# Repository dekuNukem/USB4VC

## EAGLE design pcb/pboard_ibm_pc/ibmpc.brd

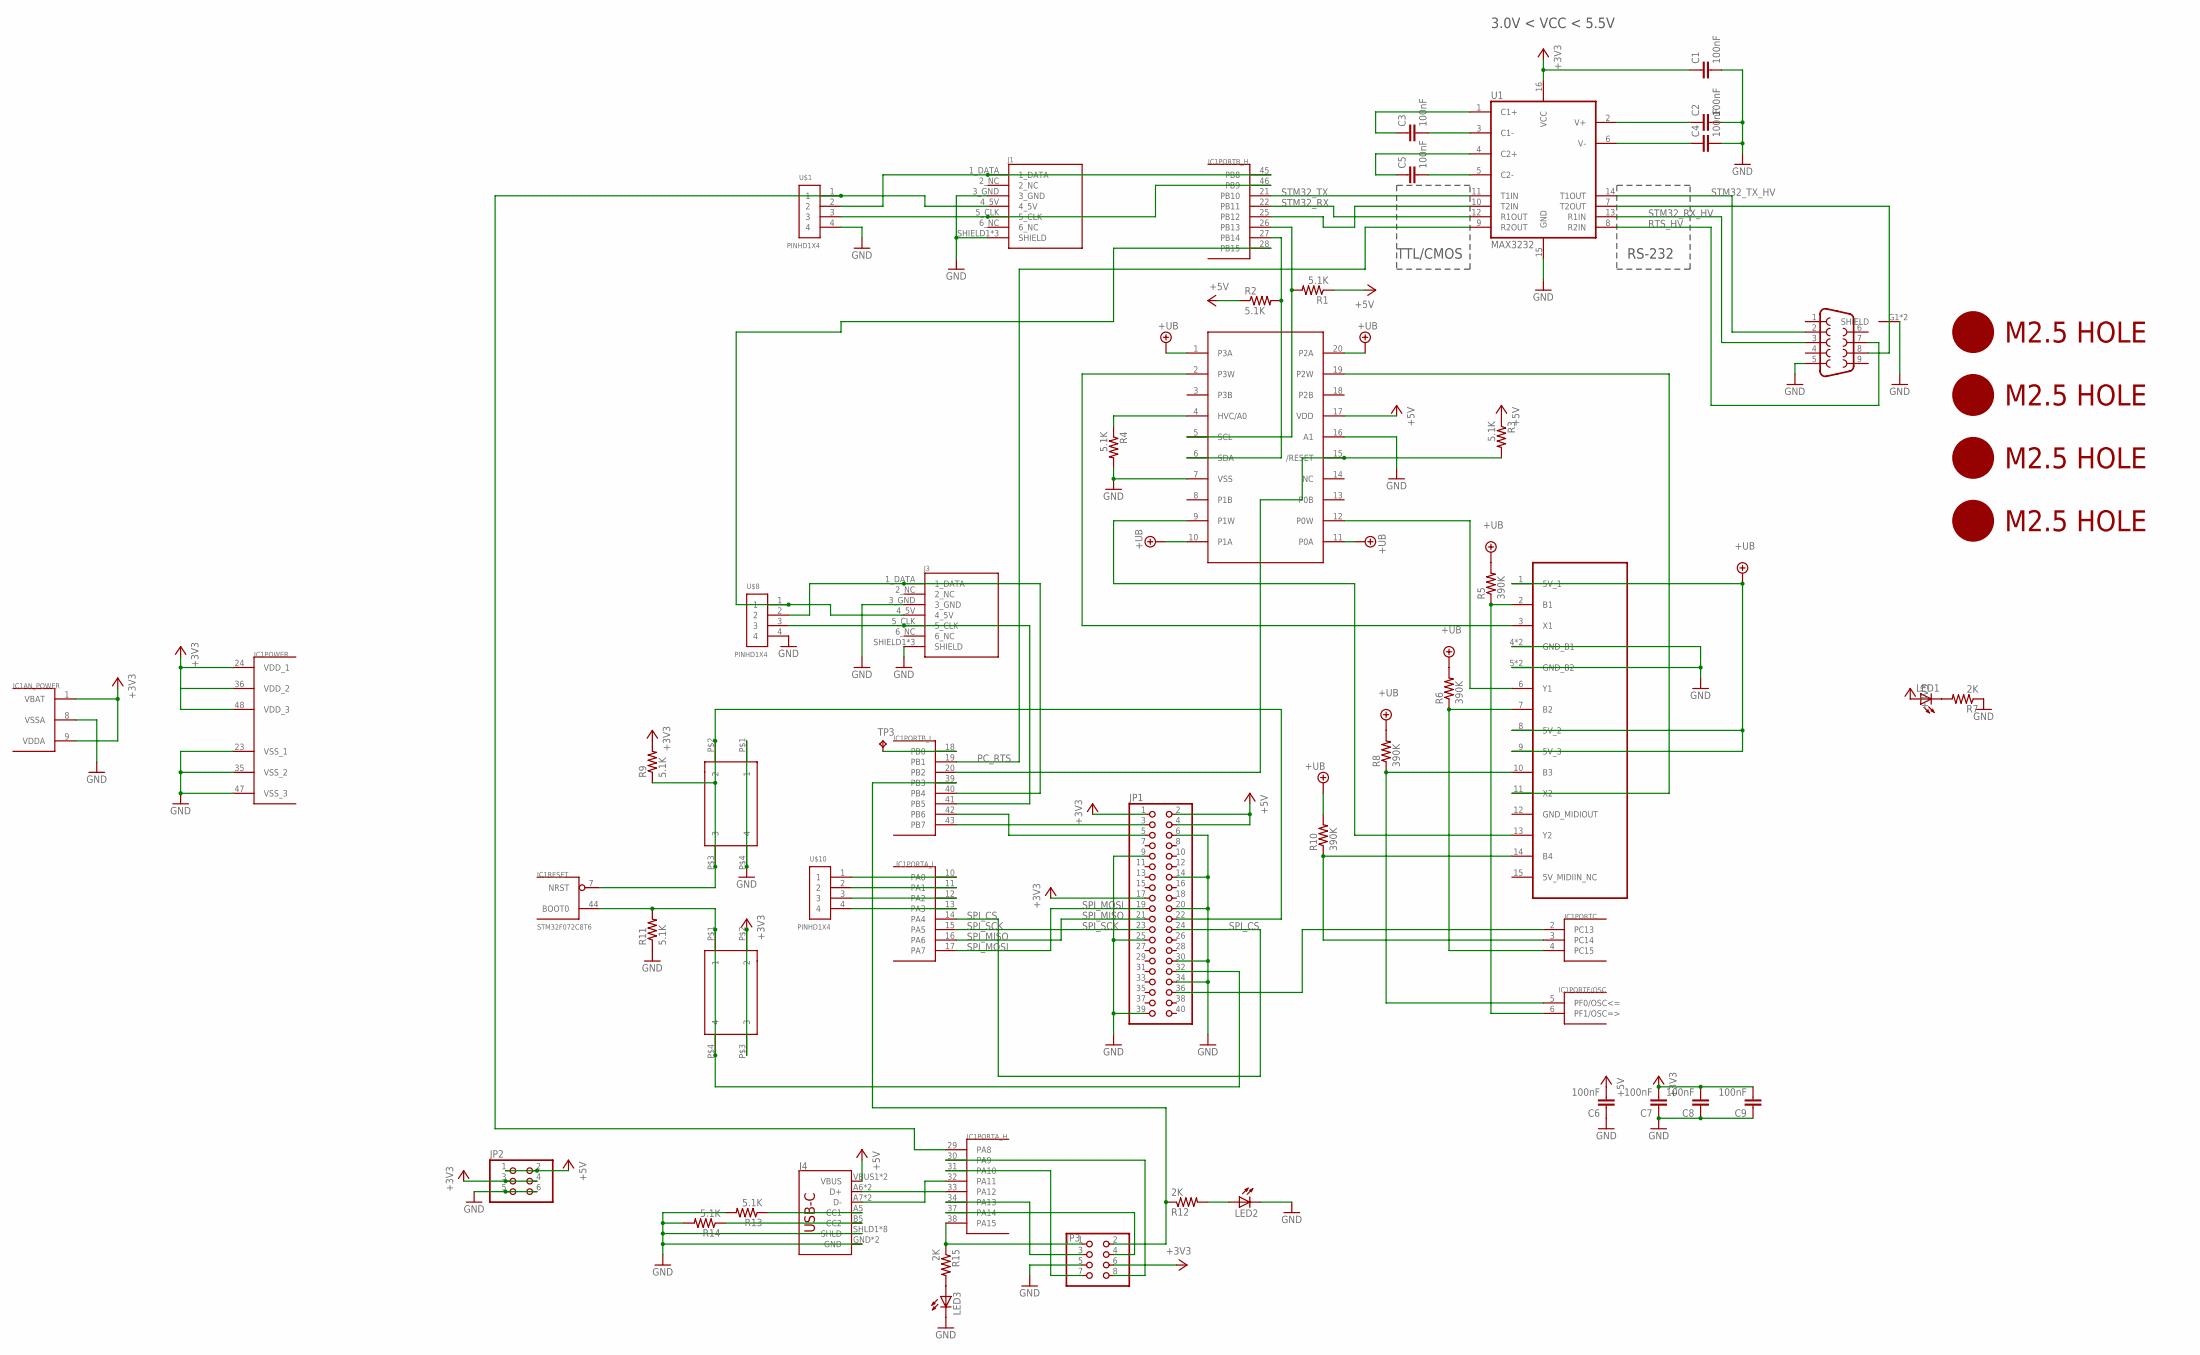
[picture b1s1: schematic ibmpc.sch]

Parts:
C1, C2, C3, C4, C5, C6, C7, C8, C9: 100nF; 0805@1
IC1: STM32F072C8T6; TQFP48
J1, J3: DIN7
J2: DB9MALE; DB9_MALE
J4: USB_C16PIN; USB-C-16P
JP1: PINHD-2X20-BIG; 2X20-BIG
JP2: PINHD-2X3; 2X03
JP3: PINHD-2X4; 2X04
LED1, LED2, LED3: LEDCHIP-LED0805; CHIP-LED0805
R1, R2, R3, R4, R9, R11, R13, R14: 5.1K; 0805
R5, R6, R8, R10: 390K; 0805
R7, R12, R15: 2K; 0805
SW1, SW2: 324_SW; 342_SWICH_FOOT
TP3: TPTP12R; TP12R
U1: MAX3232; SO016
U$1, U$8, U$10: PINHD1X4; 1X04-CLEANBIG
U$2, U$3, U$6, U$7: M2.5HOLE
U$5: MCP4451; TSSOP20
U$9: GAMEPORT_15P; DA15

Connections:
+3V3: C1.1, C7.2, C8.2, C9.2, IC1.1 (VBAT), IC1.9 (VDDA), IC1.24 (VDD_1), IC1.36 (VDD_2), IC1.48 (VDD_3), JP1.1, JP1.17, JP2.3, JP2.4, JP3.6, LED1.A, R9.2, SW2.P$2 (2), SW2.P$3 (3), U1.16 (VCC)
+5V: C6.2, J4.VBUS1 (VBUS), J4.VBUS2 (VBUS), JP1.2, JP1.4, JP2.1, JP2.2, R1.1, R2.1, R3.1, U$5.17 (VDD)
+UB: R5.2, R6.2, R8.2, R10.2, U$5.1 (P3A), U$5.10 (P1A), U$5.11 (P0A), U$5.20 (P2A), U$9.1 (5V_1), U$9.8 (5V_2), U$9.9 (5V_3)
C1+: C3.1, U1.1 (C1+)
C1-: C3.2, U1.3 (C1-)
C2+: C5.1, U1.4 (C2+)
C2-: C5.2, U1.5 (C2-)
GND: C1.2, C2.2, C4.2, C6.1, C7.1, C8.1, C9.1, IC1.8 (VSSA), IC1.23 (VSS_1), IC1.35 (VSS_2), IC1.47 (VSS_3), J1.3_GND, J1.SHIELD1 (SHIELD), J1.SHIELD2 (SHIELD), J1.SHIELD3 (SHIELD), J2.5, J2.G1 (SHIELD), J2.G2 (SHIELD), J3.3_GND, J3.SHIELD1 (SHIELD), J3.SHIELD2 (SHIELD), J3.SHIELD3 (SHIELD), J4.GND, J4.GND2 (GND), J4.SHLD1 (SHLD), J4.SHLD2 (SHLD), J4.SHLD3 (SHLD), J4.SHLD4 (SHLD), J4.SHLD5 (SHLD), J4.SHLD6 (SHLD), J4.SHLD7 (SHLD), J4.SHLD8 (SHLD), JP1.6, JP1.9, JP1.14, JP1.20, JP1.25, JP1.30, JP1.34, JP1.39, JP2.5, JP2.6, JP3.5, LED2.C, LED3.C, R4.2, R7.1, R11.1, R13.2, R14.2, SW1.P$1 (1), SW1.P$4 (4), U1.15 (GND), U$1.4, U$5.7 (VSS), U$5.16 (A1), U$8.4, U$9.4 (GND_B1), U$9.5 (GND_B2), U$9.G1 (GND_B1), U$9.G2 (GND_B2)
unnamed: J4.A5 (CC1), R13.1
unnamed: LED2.A, R12.2
unnamed: IC1.29 (PA8), J1.4_5V, U$1.1
unnamed: IC1.41 (PB5), J3.5_CLK, U$8.3
unnamed: IC1.39 (PB3), JP3.2, R12.1
unnamed: J4.B5 (CC2), R14.1
unnamed: IC1.33 (PA12), J4.A6 (D+), J4.B6 (D+)
unnamed: IC1.32 (PA11), J4.A7 (D-), J4.B7 (D-)
unnamed: IC1.45 (PB8), J1.1_DATA, U$1.2
unnamed: IC1.46 (PB9), J1.5_CLK, U$1.3
unnamed: IC1.31 (PA10), JP3.7
unnamed: IC1.7 (NRST), JP1.22, R9.1, SW1.P$2 (2), SW1.P$3 (3)
unnamed: IC1.30 (PA9), JP3.8
unnamed: IC1.34 (PA13), JP3.3
unnamed: IC1.37 (PA14), JP3.4
unnamed: IC1.44 (BOOT0), JP1.32, R11.2, SW2.P$1 (1), SW2.P$4 (4)
unnamed: IC1.4 (PC15), R6.1, U$9.7 (B2)
unnamed: IC1.5 (PF0/OSC<=), R8.1, U$9.10 (B3)
unnamed: IC1.3 (PC14), R10.1, U$9.14 (B4)
unnamed: IC1.42 (PB6), JP1.5
unnamed: IC1.43 (PB7), JP1.3
unnamed: IC1.25 (PB12), U1.10 (T2IN)
unnamed: J2.8, U1.7 (T2OUT)
unnamed: IC1.40 (PB4), J3.1_DATA, U$8.2
unnamed: IC1.38 (PA15), JP3.1, R15.1
unnamed: LED3.A, R15.2
unnamed: LED1.C, R7.2
unnamed: IC1.6 (PF1/OSC=>), R5.1, U$9.2 (B1)
unnamed: R4.1, U$5.4 (HVC/A0)
unnamed: IC1.2 (PC13), JP1.36
unnamed: IC1.10 (PA0), U$10.1
unnamed: IC1.11 (PA1), U$10.2
unnamed: IC1.12 (PA2), U$10.3
unnamed: IC1.13 (PA3), U$10.4
unnamed: IC1.28 (PB15), J3.4_5V, U$8.1
unnamed: IC1.20 (PB2), R3.2, U$5.15 (/RESET)
unnamed: IC1.18 (PB0), TP3.TP
PC_RTS: IC1.19 (PB1), U1.9 (R2OUT)
POT_SCL: IC1.26 (PB13), R1.2, U$5.5 (SCL)
PST_SDA: IC1.27 (PB14), R2.2, U$5.6 (SDA)
RTS_HV: J2.7, U1.8 (R2IN)
SPI_CS: IC1.14 (PA4), JP1.24
SPI_MISO: IC1.16 (PA6), JP1.21
SPI_MOSI: IC1.17 (PA7), JP1.19
SPI_SCK: IC1.15 (PA5), JP1.23
STM32_RX: IC1.22 (PB11), U1.12 (R1OUT)
STM32_RX_HV: J2.3, U1.13 (R1IN)
STM32_TX: IC1.21 (PB10), U1.11 (T1IN)
STM32_TX_HV: J2.2, U1.14 (T1OUT)
V+: C2.1, U1.2 (V+)
V-: C4.1, U1.6 (V-)
X1_W3: U$5.2 (P3W), U$9.3 (X1)
X2_W2: U$5.19 (P2W), U$9.11 (X2)
Y1_W0: U$5.12 (P0W), U$9.6 (Y1)
Y2_W1: U$5.9 (P1W), U$9.13 (Y2)

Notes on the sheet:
RS-232
TTL/CMOS
3.0V < VCC < 5.5V

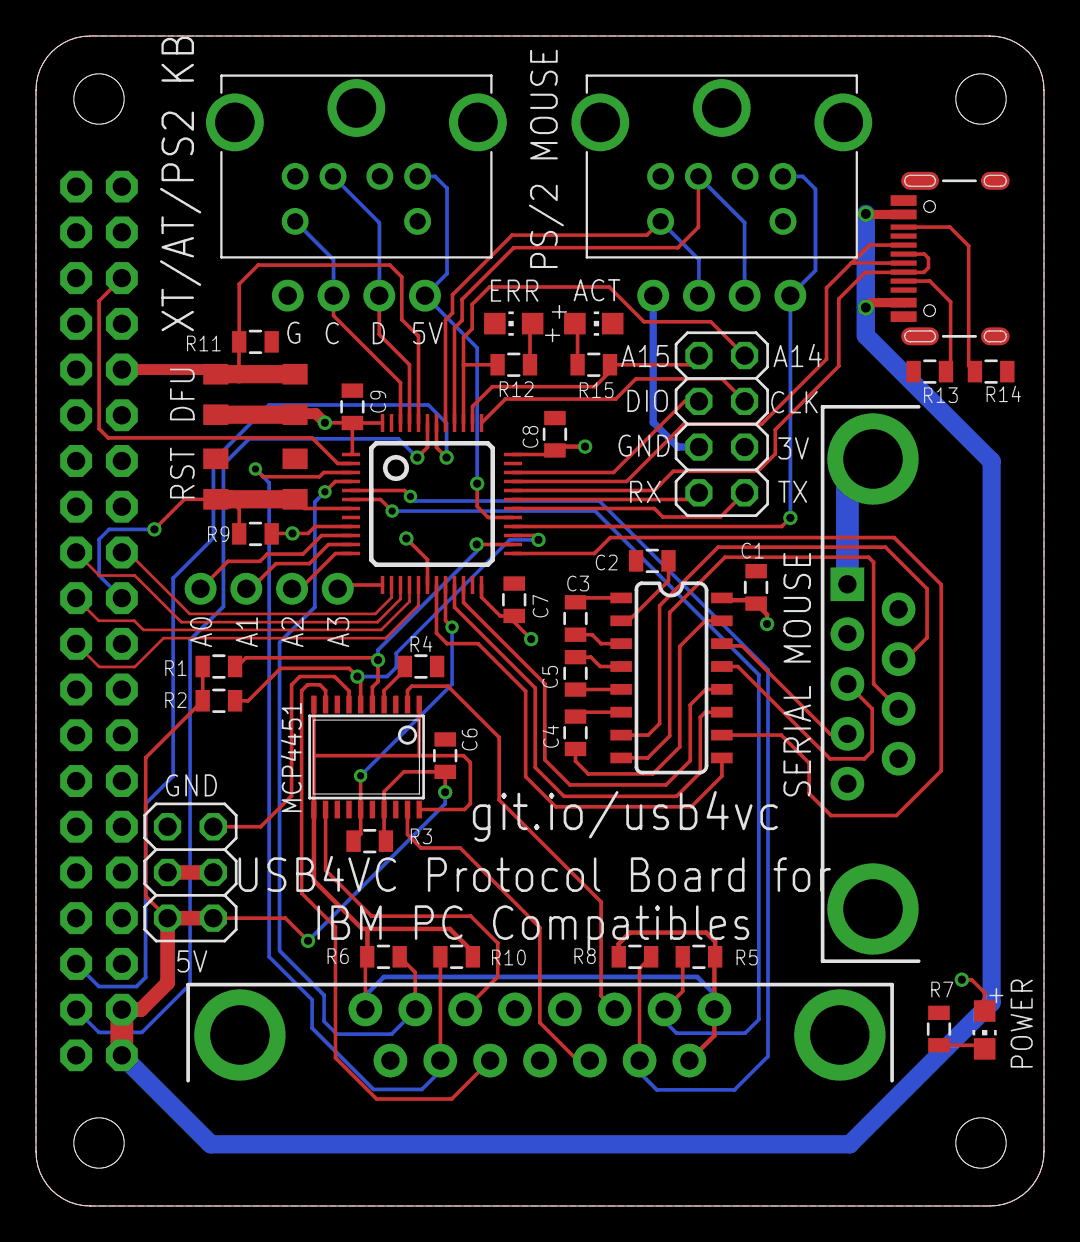
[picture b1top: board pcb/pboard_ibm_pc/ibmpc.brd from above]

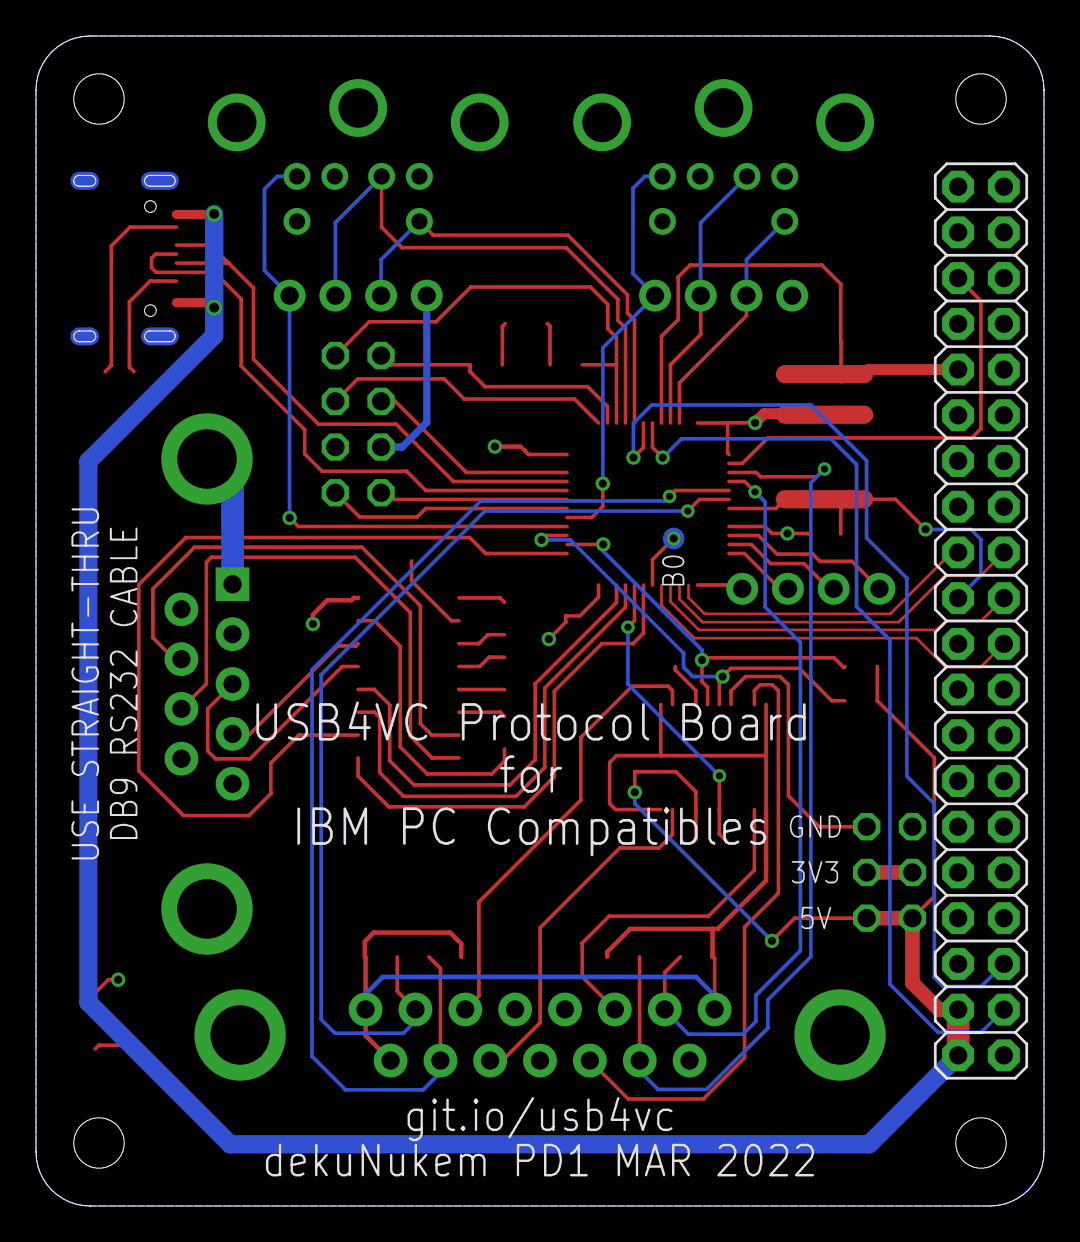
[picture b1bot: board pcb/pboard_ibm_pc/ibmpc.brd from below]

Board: 2 copper layers, 56.0 x 65.0 mm, 48 parts (2 on the bottom side), 63 nets.

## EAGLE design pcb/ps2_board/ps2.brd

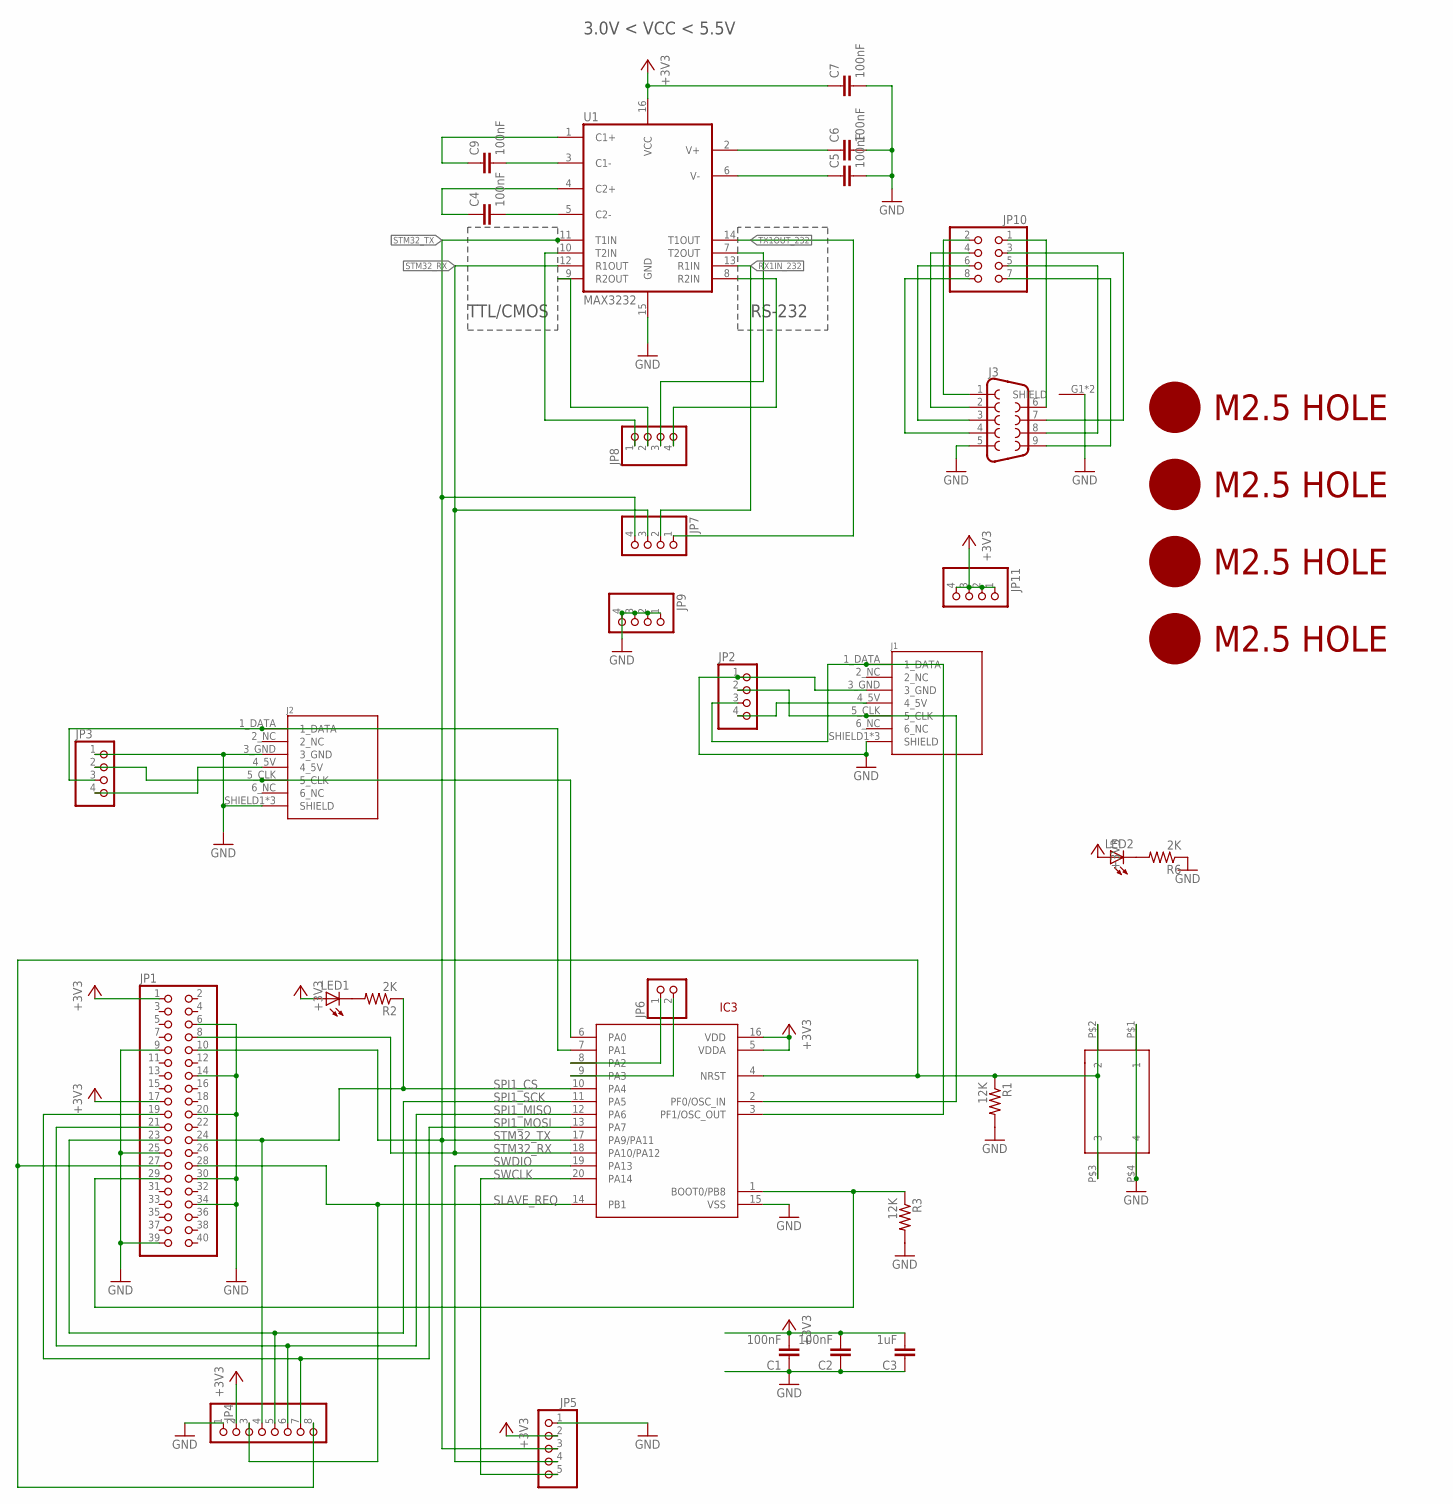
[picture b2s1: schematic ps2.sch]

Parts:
C1, C2, C4, C5, C6, C7, C9: 100nF; 0805@1
C3: 1uF; 0805@1
IC3: STM32F042F4; TSSOP20
J1, J2: DIN7
J3: DB9MALE; DB9_MALE
JP1: PINHD-2X20-BIG; 2X20-BIG
JP2, JP3, JP7, JP8, JP9, JP11: PINHD-1X4; 1X04
JP4: PINHD-1X8; 1X08
JP5: PINHD-1X5; 1X05
JP6: PINHD-1X2; 1X02
JP10: PINHD-2X4; 2X04
LED1, LED2: LEDCHIP-LED0805; CHIP-LED0805
R1, R3: 12K; 0805
R2, R6: 2K; 0805
SW4: 324_SW; 342_SWICH_FOOT
U1: MAX3232; SO016
U$2, U$3, U$4, U$5: M2.5HOLE

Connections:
+3V3: C1.2, C2.2, C3.2, C7.1, IC3.5 (VDDA), IC3.16 (VDD), JP1.1, JP1.17, JP4.2, JP5.2, JP11.1, JP11.2, JP11.3, JP11.4, LED1.A, LED2.A, U1.16 (VCC)
C1+: C9.1, U1.1 (C1+)
C1-: C9.2, U1.3 (C1-)
C2+: C4.1, U1.4 (C2+)
C2-: C4.2, U1.5 (C2-)
GND: C1.1, C2.1, C3.1, C5.2, C6.2, C7.2, IC3.15 (VSS), J1.3_GND, J1.SHIELD1 (SHIELD), J1.SHIELD2 (SHIELD), J1.SHIELD3 (SHIELD), J2.3_GND, J2.SHIELD1 (SHIELD), J2.SHIELD2 (SHIELD), J2.SHIELD3 (SHIELD), J3.5, J3.G1 (SHIELD), J3.G2 (SHIELD), JP1.6, JP1.9, JP1.14, JP1.20, JP1.25, JP1.30, JP1.34, JP1.39, JP2.1, JP3.1, JP4.1, JP5.1, JP9.1, JP9.2, JP9.3, JP9.4, R1.2, R3.2, R6.1, SW4.P$1 (1), SW4.P$4 (4), U1.15 (GND)
unnamed: IC3.4 (NRST), JP1.27, JP4.8, R1.1, SW4.P$2 (2), SW4.P$3 (3)
unnamed: LED1.C, R2.2
unnamed: J1.4_5V, JP2.4
unnamed: J2.4_5V, JP3.4
unnamed: IC3.2 (PF0/OSC_IN), J1.5_CLK, JP2.2
unnamed: IC3.3 (PF1/OSC_OUT), J1.1_DATA, JP2.3
unnamed: IC3.6 (PA0), J2.5_CLK, JP3.2
unnamed: IC3.7 (PA1), J2.1_DATA, JP3.3
unnamed: IC3.1 (BOOT0/PB8), JP1.29, R3.1
unnamed: IC3.8 (PA2), JP6.1
unnamed: IC3.9 (PA3), JP6.2
unnamed: JP8.1, U1.10 (T2IN)
unnamed: JP8.2, U1.9 (R2OUT)
unnamed: JP8.3, U1.7 (T2OUT)
unnamed: JP8.4, U1.8 (R2IN)
unnamed: J3.1, JP10.2
unnamed: J3.2, JP10.4
unnamed: J3.3, JP10.6
unnamed: J3.4, JP10.8
unnamed: J3.6, JP10.1
unnamed: J3.7, JP10.3
unnamed: J3.8, JP10.5
unnamed: J3.9, JP10.7
unnamed: LED2.C, R6.2
RX1IN_232: JP7.2, U1.13 (R1IN)
SLAVE_REQ: IC3.14 (PB1), JP1.28, JP4.3
SPI1_CS: IC3.10 (PA4), JP1.24, JP4.4, R2.1
SPI1_MISO: IC3.12 (PA6), JP1.21, JP4.6
SPI1_MOSI: IC3.13 (PA7), JP1.19, JP4.7
SPI1_SCK: IC3.11 (PA5), JP1.23, JP4.5
STM32_RX: IC3.18 (PA10/PA12), JP1.8, JP7.3, U1.12 (R1OUT)
STM32_TX: IC3.17 (PA9/PA11), JP1.10, JP5.3, JP7.4, U1.11 (T1IN)
SWCLK: IC3.20 (PA14), JP5.5
SWDIO: IC3.19 (PA13), JP5.4
TX1OUT_232: JP7.1, U1.14 (T1OUT)
V+: C6.1, U1.2 (V+)
V-: C5.1, U1.6 (V-)

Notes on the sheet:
RS-232
TTL/CMOS
3.0V < VCC < 5.5V

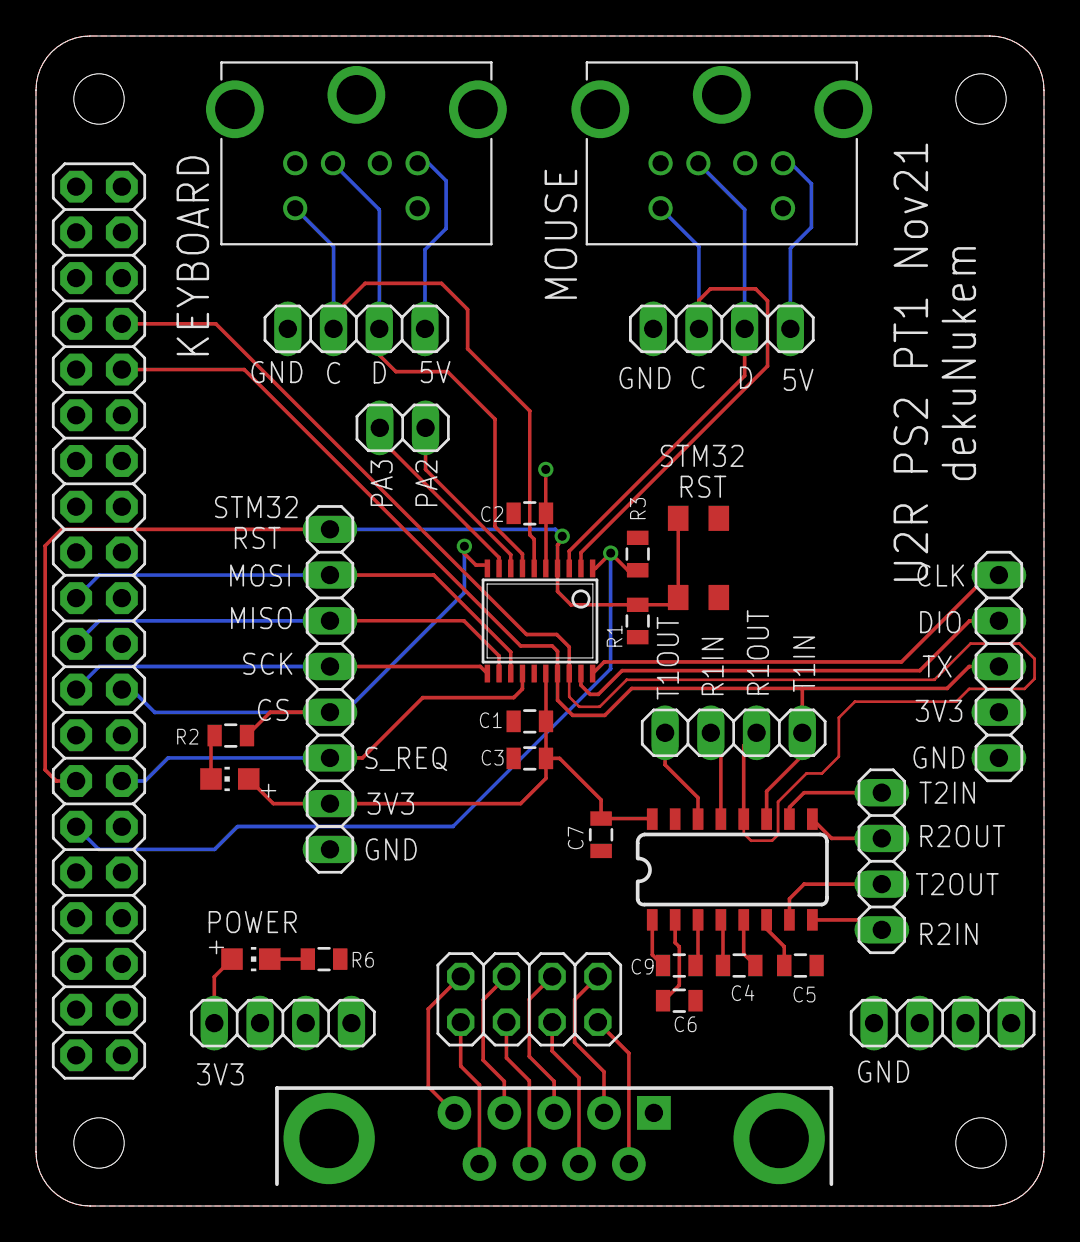
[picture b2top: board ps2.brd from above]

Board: 2 copper layers, 56.0 x 65.0 mm, 35 parts (0 on the bottom side), 43 nets.

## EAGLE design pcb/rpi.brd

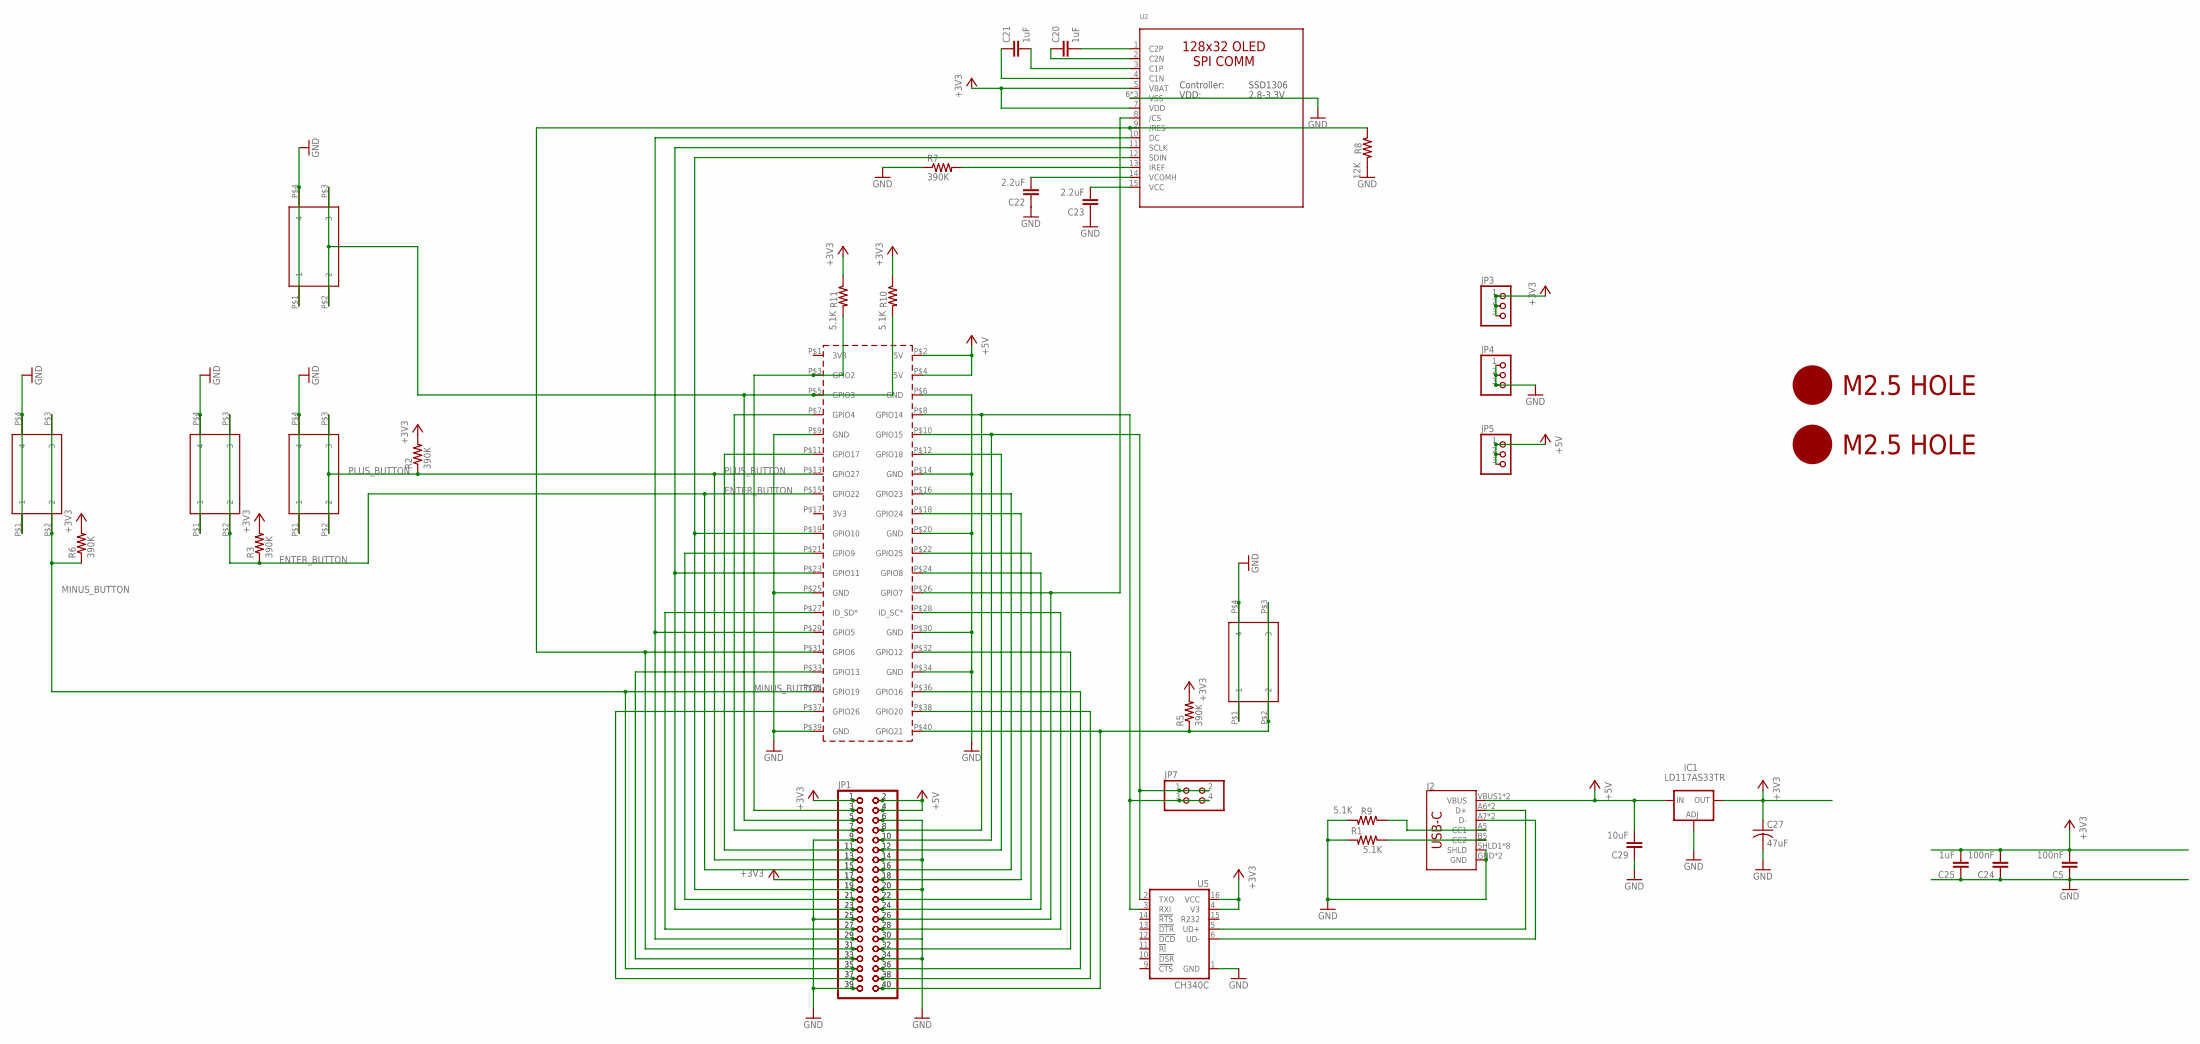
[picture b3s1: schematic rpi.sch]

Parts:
C5, C24: 100nF; 0805
C20, C21, C25: 1uF; 0805
C22, C23: 2.2uF; 0805
C27: 47uF; C1210
C29: 10uF; 0805
IC1: LD117AS33TR; SOT223
J2: USB_C16PIN; USB-C-16P
JP1, JP2: PINHD-2X20-BIG; 2X20-BIG
JP3, JP4, JP5: PINHD-1X3; 1X03
JP7: PINHD-2X2; 2X02
PCB1: RPI3NO-CONNECTORS; RPI3-NO-CONNECTORS
R1, R9, R10, R11: 5.1K; 0805
R2, R3, R5, R6, R7: 390K; 0805
R8: 12K; 0805
SW1, SW2, SW3, SW4, SW20: 324_SW; 342_SWICH_FOOT
U2: LUL_DISP_OLED_UG-2864HSWEG01; LUL_UG-2864HSWEG01_1.3_WRAPAROUND
U5: CH340C; SO016
U$2, U$3: M2.5HOLE

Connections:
+3V3: C5.2, C24.2, C25.2, C27.1, IC1.4 (OUT), JP1.1, JP1.17, JP2.1, JP2.17, JP3.1, JP3.2, JP3.3, R2.2, R3.2, R5.2, R6.2, R10.1, R11.1, U2.5 (VBAT), U2.7 (VDD), U5.4 (V3), U5.16 (VCC)
+5V: C29.2, IC1.3 (IN), J2.VBUS1 (VBUS), J2.VBUS2 (VBUS), JP1.2, JP1.4, JP2.2, JP2.4, JP5.1, JP5.2, JP5.3, PCB1.P$2 (5V), PCB1.P$4 (5V)
ENTER_BUTTON: JP1.15, JP2.15, PCB1.P$15 (GPIO22), R3.1, SW20.P$2 (2), SW20.P$3 (3)
GND: C5.1, C22.1, C23.1, C24.1, C25.1, C27.2, C29.1, IC1.1 (ADJ), J2.GND, J2.GND2 (GND), J2.SHLD1 (SHLD), J2.SHLD2 (SHLD), J2.SHLD3 (SHLD), J2.SHLD4 (SHLD), J2.SHLD5 (SHLD), J2.SHLD6 (SHLD), J2.SHLD7 (SHLD), J2.SHLD8 (SHLD), JP1.6, JP1.9, JP1.14, JP1.20, JP1.25, JP1.30, JP1.34, JP1.39, JP2.6, JP2.9, JP2.14, JP2.20, JP2.25, JP2.30, JP2.34, JP2.39, JP4.1, JP4.2, JP4.3, PCB1.P$6 (GND), PCB1.P$9 (GND), PCB1.P$14 (GND), PCB1.P$20 (GND), PCB1.P$25 (GND), PCB1.P$30 (GND), PCB1.P$34 (GND), PCB1.P$39 (GND), R1.2, R7.1, R8.2, R9.2, SW1.P$1 (1), SW1.P$4 (4), SW2.P$1 (1), SW2.P$4 (4), SW3.P$1 (1), SW3.P$4 (4), SW4.P$1 (1), SW4.P$4 (4), SW20.P$1 (1), SW20.P$4 (4), U2.6 (VSS), U2.16 (VSS), U2.17 (VSS), U5.1 (GND)
MINUS_BUTTON: JP1.35, JP2.35, PCB1.P$35 (GPIO19), R6.1, SW4.P$2 (2), SW4.P$3 (3)
unnamed: J2.A6 (D+), J2.B6 (D+), U5.5 (UD+)
unnamed: J2.A5 (CC1), R9.1
unnamed: J2.A7 (D-), J2.B7 (D-), U5.6 (UD-)
unnamed: JP1.3, JP2.3, PCB1.P$3 (GPIO2), R11.2
unnamed: JP1.5, JP2.5, PCB1.P$5 (GPIO3), R10.2, SW2.P$2 (2), SW2.P$3 (3)
unnamed: J2.B5 (CC2), R1.1
unnamed: JP1.7, JP2.7, PCB1.P$7 (GPIO4)
unnamed: JP1.11, JP2.11, PCB1.P$11 (GPIO17)
unnamed: JP1.19, JP2.19, PCB1.P$19 (GPIO10), U2.12 (SDIN)
unnamed: JP1.21, JP2.21, PCB1.P$21 (GPIO9)
unnamed: JP1.23, JP2.23, PCB1.P$23 (GPIO11), U2.11 (SCLK)
unnamed: JP1.27, JP2.27, PCB1.P$27 (ID_SD*)
unnamed: JP1.29, JP2.29, PCB1.P$29 (GPIO5), U2.10 (DC)
unnamed: JP1.33, JP2.33, PCB1.P$33 (GPIO13)
unnamed: JP1.37, JP2.37, PCB1.P$37 (GPIO26)
unnamed: JP1.12, JP2.12, PCB1.P$12 (GPIO18)
unnamed: JP1.16, JP2.16, PCB1.P$16 (GPIO23)
unnamed: JP1.18, JP2.18, PCB1.P$18 (GPIO24)
unnamed: JP1.22, JP2.22, PCB1.P$22 (GPIO25)
unnamed: JP1.24, JP2.24, PCB1.P$24 (GPIO8)
unnamed: JP1.26, JP2.26, PCB1.P$26 (GPIO7), U2.8 (/CS)
unnamed: JP1.28, JP2.28, PCB1.P$28 (ID_SC*)
unnamed: JP1.32, JP2.32, PCB1.P$32 (GPIO12)
unnamed: JP1.36, JP2.36, PCB1.P$36 (GPIO16)
unnamed: JP1.38, JP2.38, PCB1.P$38 (GPIO20)
unnamed: JP1.40, JP2.40, PCB1.P$40 (GPIO21), R5.1, SW3.P$2 (2), SW3.P$3 (3)
unnamed: C20.2, U2.1 (C2P)
unnamed: C20.1, U2.2 (C2N)
unnamed: C21.2, U2.3 (C1P)
unnamed: C21.1, U2.4 (C1N)
unnamed: R7.2, U2.13 (IREF)
unnamed: C22.2, U2.14 (VCOMH)
unnamed: C23.2, U2.15 (VCC)
unnamed: JP1.31, JP2.31, PCB1.P$31 (GPIO6), R8.1, U2.9 (/RES)
PLUS_BUTTON: JP1.13, JP2.13, PCB1.P$13 (GPIO27), R2.1, SW1.P$2 (2), SW1.P$3 (3)
RPI_RX: JP1.10, JP2.10, JP7.1, JP7.2, PCB1.P$10 (GPIO15), U5.2 (TXO)
RPI_TX: JP1.8, JP2.8, JP7.3, JP7.4, PCB1.P$8 (GPIO14), U5.3 (RXI)

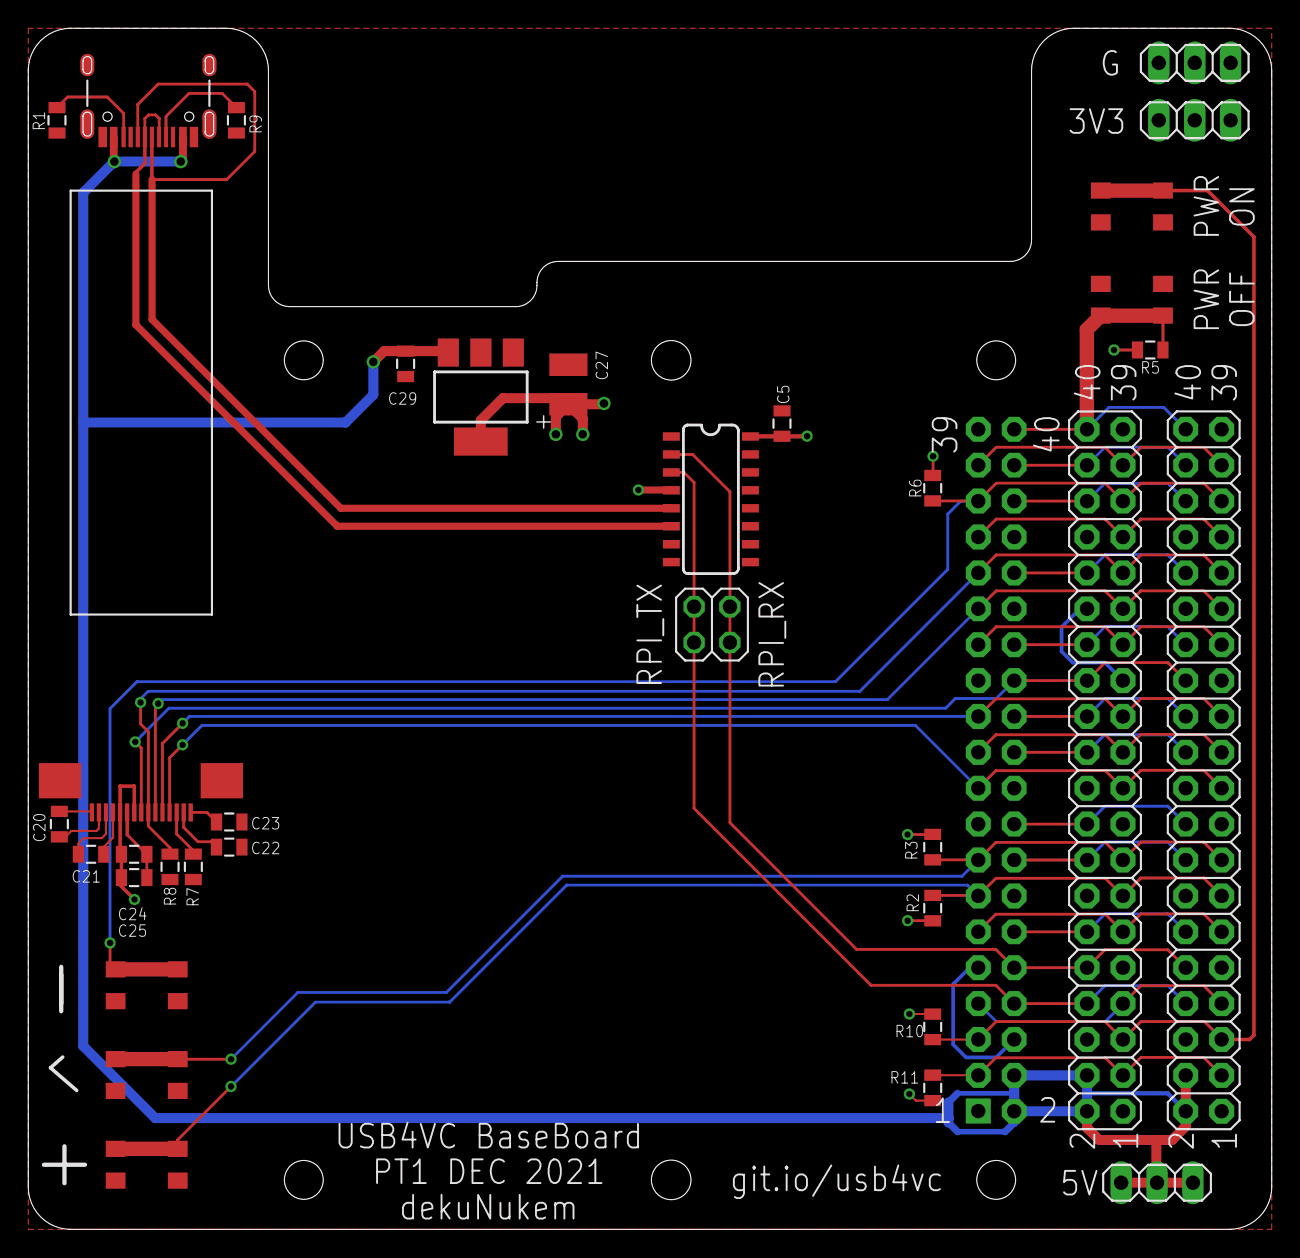
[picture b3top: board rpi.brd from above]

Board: 2 copper layers, 88.0 x 85.0 mm, 37 parts (0 on the bottom side), 42 nets.

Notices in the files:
parts and their libraries:
SparkFun-Connectors: Licensing: Creative Commons ShareAlike 4.0 International - https://creativecommons.org/licenses/by-sa/4.0
SparkFun-Aesthetics: Licensing: CC v3.0 Share-Alike You are welcome to use this library for commercial purposes.
